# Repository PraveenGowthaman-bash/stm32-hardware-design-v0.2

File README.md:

# stm32-hardware-design-v0.2
Complete STM32F4 PCB design with full manufacturing package - My first MCU board design

## 📋 Project Overview
My first complete STM32 microcontroller board design from scratch. This project represents my journey from following tutorials to independent hardware design.

**Key Features:**
- STM32F103F6CT8 microcontroller (ARM Cortex-M4, 168MHz)
- USB 2.0 Full Speed interface
- UART, I2C, SPI breakout headers
- Proper power supply filtering (digital/analog separation)
- SWD debug interface
- User-configurable boot modes

## 🎯 Design Goals
1. Learn professional PCB design workflow
2. Understand STM32 power architecture
3. Practice manufacturable design (DRC/DFM)
4. Create complete manufacturing package

## 📁 Repository Structure

## 🛠️ Design Decisions & Lessons Learned

### Power Supply Design
- Used AMS1117-3.3v LDO for clean 3.3V rail
- Separate VDDA supply with ferrite bead isolation
- Proper decoupling: 10µF bulk + 100nF per pin + 10nF high-frequency

### Component Selection
- **0603 package** chosen over 0402 for better manufacturability
- Crystal oscillator with 20ppm stability for USB compliance
- Reset circuit with debouncing capacitor

### PCB Layout
- 2-layer design (cost-effective for learning)
- Controlled impedance where possible
- Proper ground plane stitching
- Manufacturing-friendly clearances (0.15mm minimum)

## 🔧 Manufacturing Instructions

### Ordering PCBs
1. Upload all files in `manufacturing/gerber/` to JLCPCB/PCBWay
2. Use standard 1.6mm FR-4, HASL finish
3. Minimum clearance: 0.15mm (6mil)

## 📈 Version History
- **v0.1** - Initial design, DRC clearance issues with 0402 components
- **v0.2** - Fixed DRC issues with 0603 components, improved layout, complete manufacturing package

## 📚 Resources & References
- [Phil's Lab Tutorials](https://www.youtube.com/c/PhilsLab)

## 👨‍💻 About the Designer
Final year electronics student learning hardware design through hands-on projects. This board represents my transition from tutorial-following to independent design.

---
*If you build this board or have suggestions, please open an issue or pull request!*

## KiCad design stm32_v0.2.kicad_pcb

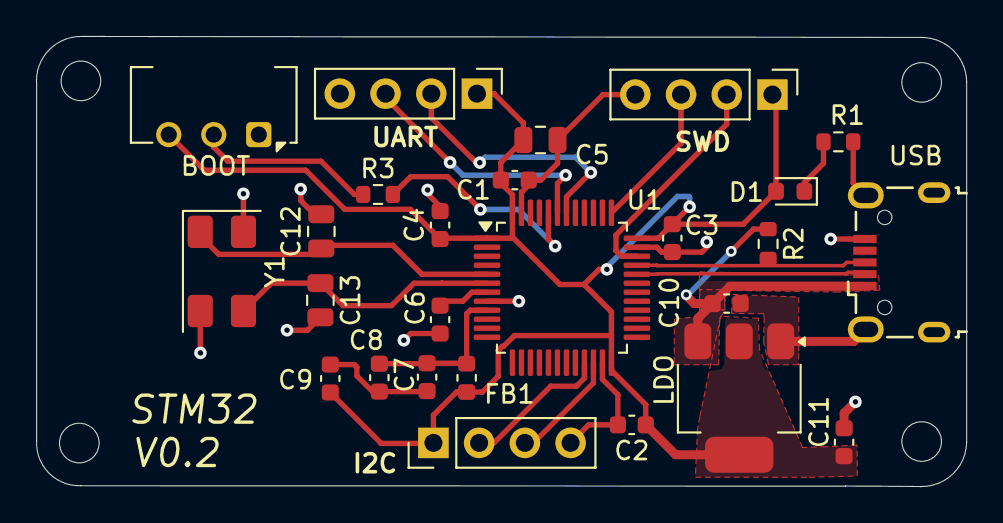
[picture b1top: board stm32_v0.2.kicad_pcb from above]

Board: 2 copper layers, 51.7 x 25.0 mm, 30 parts (0 on the bottom side), 19 nets.

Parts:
BOOT: SW_DPDT_x2; SW_CK_JS202011AQN_DPDT_Angled
C1, C2, C3, C4, C6, C7, C8, C9, C10, C11: 100n; C_0603_1608Metric
C5: 10u; C_0805_2012Metric
C12, C13: 20p; C_0805_2012Metric
D1: LED; LED_0603_1608Metric
FB1: FerriteBead; L_0603_1608Metric
H1, H2, H3, H4: MountingHole; MountingHole_2.2mm_M2
I2C: Conn_01x04_Pin; PinHeader_1x04_P2.54mm_Vertical
LDO: AMS1117-3.3; SOT-223-3_TabPin2
R1: 1k5; R_0603_1608Metric
R2, R3: 1K5; R_0603_1608Metric
SWD: Conn_01x04_Pin; PinHeader_1x04_P2.54mm_Vertical
U1: STM32F103C6T8; LQFP-48_7x7mm_P0.5mm
UART: Conn_01x04_Pin; PinHeader_1x04_P2.54mm_Vertical
USB: USB_B_Micro; USB_Micro-B_Wuerth_629105150521
Y1: Crystal_GND24; Crystal_SMD_0603-4Pin_6.0x3.5mm

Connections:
+3.3V: BOOT.3 (C), C1.1, C2.1, C3.1, C4.1, C5.1, C9.1, C11.1, D1.2 (A), FB1.2, I2C.1, LDO.2 (VO), SWD.1, U1.1 (VBAT), U1.24 (VDD), U1.36 (VDD), U1.48 (VDD), UART.1
+3.3VA: C7.1, C8.1, FB1.1, U1.9 (VDDA)
/BOOT0: R3.2, U1.44 (BOOT0)
/HS_OSC_IN: C12.1, U1.5 (PD0), Y1.1
/HS_OSC_OUT: C13.1, U1.6 (PD1), Y1.3
/I2C2_SCL: I2C.2, U1.21 (PB10)
/I2C2_SDA: I2C.3, U1.22 (PB11)
/SWCLK: SWD.3, U1.37 (PA14)
/SWDIO: SWD.2, U1.34 (PA13)
/SW_BOOT: BOOT.2 (B), R3.1
/USART1_RX: U1.43 (PB7), UART.3
/USART1_TX: U1.42 (PB6), UART.2
/USB_D+: R2.2, U1.33 (PA12), USB.3 (D+)
/USB_D-: U1.32 (PA11), USB.2 (D-)
GND: BOOT.1 (A), C1.2, C2.2, C3.2, C4.2, C5.2, C6.2, C10.2, C11.2, C12.2, C13.2, I2C.4, LDO.1 (GND), R1.2, SWD.4, U1.8 (VSSA), U1.23 (VSS), U1.35 (VSS), U1.47 (VSS), UART.4, USB.5 (GND), USB.6 (Shield), Y1.2, Y1.4
unnamed: C7.2, C8.2, C9.2
unnamed: D1.1 (K), R1.1
unnamed: C6.1, U1.7 (NRST)
VBUS: C10.1, LDO.3 (VI), R2.1, USB.1 (VBUS)
